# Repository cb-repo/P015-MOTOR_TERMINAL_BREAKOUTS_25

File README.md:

# 25mm MOTOR TERMINAL BREAKOUT v1.0 (2-pack)

Motor terminals are traditionally small and flimsy, making it hard to guarantee a reliable solder connection.
MOTOR TERMINAL BREAKOUTS are designed to simplify and strengthen these solder joints, enabling more reliable operation especally in high vibration environments: orignially designed for combat robotics but is suitable for any application using these motors. 
  
This is a [New Zealand](https://www.google.co.nz/maps/place/Christchurch+New+Zealand) based product by [cb-technology](https://www.cb-technology.co.nz/), Connor Benton.

## FEATURES
- Mounts to the motor at 0°, 45°, 90°, and 135° angles
- Large solder pads enable stronger connections to the wires
- Pads are broken out onto PCB 'fingers' allowing the wires to be individually heatshrunk (providing even greater mechanical strength)
- Capacitor across the motor output to filter noise and voltage spikes

## SPECIFICATIONS
- **Dimensions:** 25x30.5x2.4 mm
- **Weight:** 1g each
- **Capacitance:** 10nF
- **Material:** Fiberglass
- **Included in Package:** 2x Motor Terminal Breakouts

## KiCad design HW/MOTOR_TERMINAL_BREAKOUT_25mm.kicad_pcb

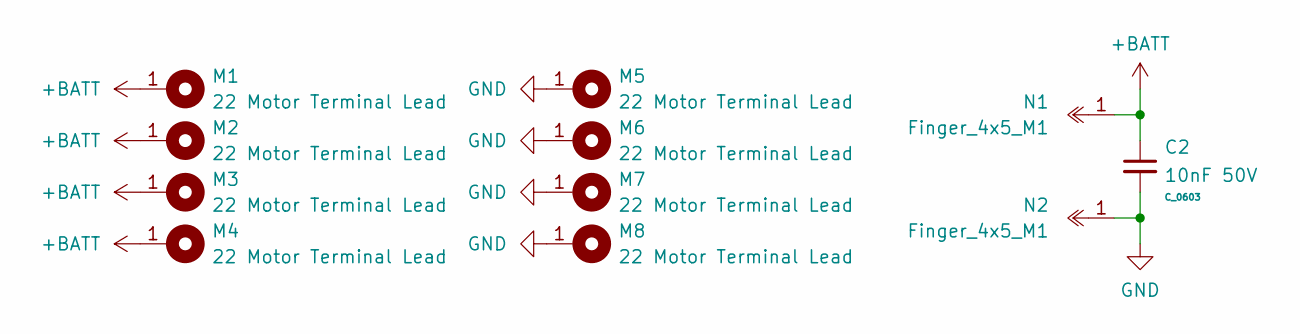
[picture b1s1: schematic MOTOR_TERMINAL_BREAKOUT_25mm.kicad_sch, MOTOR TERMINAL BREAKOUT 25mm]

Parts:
C2: 10nF 50V; C_0603; MFG Part CC0603KRX7R9BB103; LCSC_Part C100042
M1, M2, M3, M4, M5, M6, M7, M8: 22 Motor Terminal Lead
N1, N2: Finger_4x5_M1

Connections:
+BATT: C2.1, M1.1, M2.1, M3.1, M4.1, N1.1
GND: C2.2, M5.1, M6.1, M7.1, M8.1, N2.1

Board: 2 copper layers, 11 parts (0 on the bottom side), 2 nets, no tracks yet.

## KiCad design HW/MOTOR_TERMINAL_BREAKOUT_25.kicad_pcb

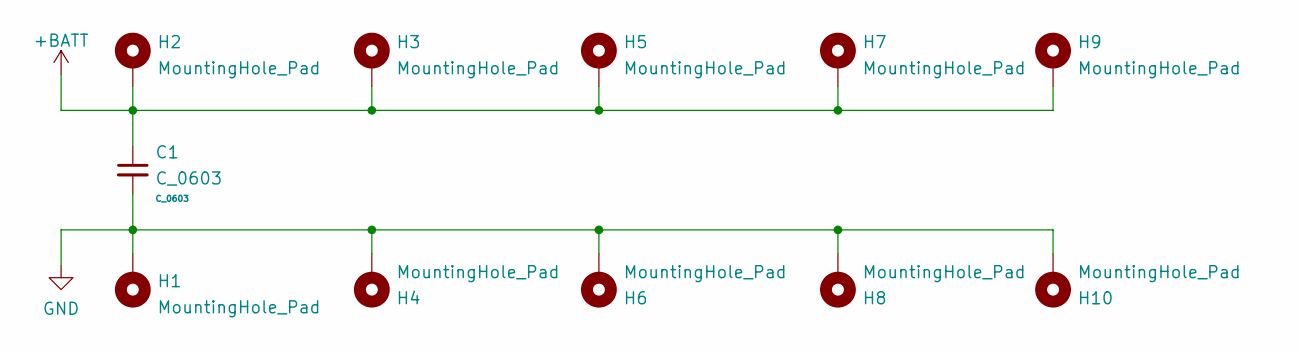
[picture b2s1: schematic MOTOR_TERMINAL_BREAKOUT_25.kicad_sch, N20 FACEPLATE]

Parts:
C1: C_0603
H1, H2: MountingHole_Pad; MountingHole_3.2mm_M3_ISO7380_Pad_TopBottom
H3, H4, H5, H6, H7, H8, H9, H10: MountingHole_Pad; MountingHole_3mm_Pad_TopBottom

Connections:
+BATT: C1.1, H2.1, H3.1, H5.1, H7.1, H9.1
GND: C1.2, H1.1, H4.1, H6.1, H8.1, H10.1

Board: 2 copper layers, 12 parts (0 on the bottom side), 2 nets, no tracks yet.

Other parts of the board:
H13: MountingHole_Pad; MountingHole_6.5mm

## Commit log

2022-07-17 Initialise LFS in Repo
2022-07-17 Generate Rev0A of the Terminal Breakout PCB
2022-07-19 Make Minor Updates to Mount Holes and Silkscreen
2022-07-31 Adjust Hole Positions to Account For Terminal Angle on Motor
2022-07-31 Add Zip File to Outputs
2022-08-09 Update README for release to CRNZ
2022-08-20 Fix issue hole position issue.
    Holes positions did not allow motor terminals to align with bolt holes
2024-04-17 Update Design for Next MFG Run
2024-06-04 Create Production Files
2024-06-04 Create Production Label
